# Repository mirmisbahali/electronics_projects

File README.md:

# LED Matrix PCB

A compact LED matrix prototyping board driven by an **Arduino Nano** using **charlieplexing** to control a large number of LEDs with minimal I/O pins.

## Status: 🚧 In Progress
- [x] Schematic complete
- [x] PCB layout complete
- [x] Fabrication files generated (JLCPCB) — parts ordered
- [ ] Testing

## Preview

### PCB View

> v1 design complete. Parts ordered from JLCPCB.

### Schematic

## Hardware
| Component | Details |
|-----------|---------|
| MCU | Arduino Nano |
| LED driver | Charlieplexing |
| Version | v1 |

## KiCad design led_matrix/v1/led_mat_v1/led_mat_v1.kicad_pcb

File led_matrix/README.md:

# LED Matrix PCB

A compact LED matrix prototyping board driven by an **Arduino Nano** using **charlieplexing** to control a large number of LEDs with minimal I/O pins.

## Status: 🚧 In Progress
- [x] Schematic complete
- [ ] PCB layout (component placement in progress)
- [ ] Fabrication
- [ ] Testing

## Preview

### PCB View

> Component placement and routing in progress.

### Schematic

## Hardware
| Component | Details |
|-----------|---------|
| MCU | Arduino Nano |
| LED driver | Charlieplexing |
| Version | v1 |

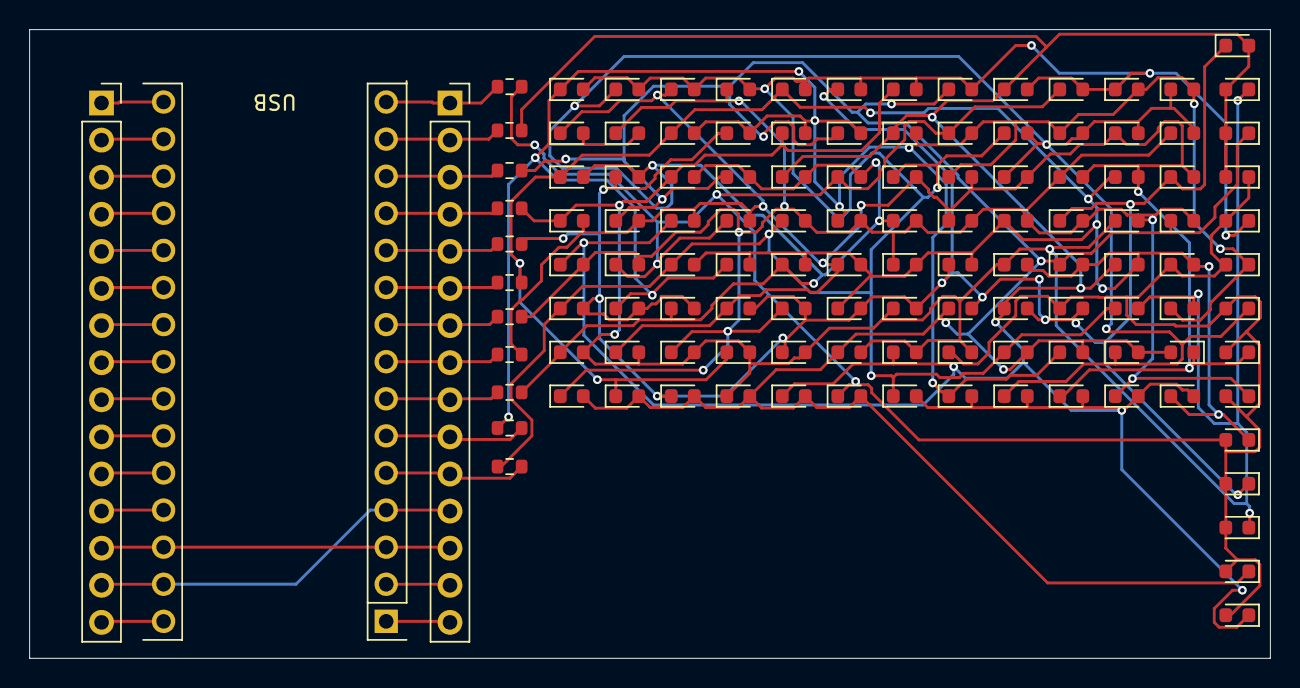
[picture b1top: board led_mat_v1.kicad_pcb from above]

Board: 2 copper layers, 85.0 x 43.1 mm, 124 parts (0 on the bottom side), 39 nets.

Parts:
A1: Arduino_Nano_Every; Arduino_Nano
D1, D2, D3, D4, D5, D6, D7, D8, D9, D10, D11, D12, D13, D14, D15, D16, D17, D18, D19, D20, D21, D22, D23, D24, D25, D26, D27, D28, D29, D30, D31, D32, D33, D34, D35, D36, D37, D38, D39, D40, D41, D42, D43, D44, D45, D46, D47, D48, D49, D50, D51, D52, D53, D54, D55, D56, D57, D58, D59, D60, D61, D62, D63, D64, D65, D66, D67, D68, D69, D70, D71, D72, D73, D74, D75, D76, D77, D78, D79, D80, D81, D82, D83, D84, D85, D86, D87, D88, D89, D90, D91, D92, D93, D94, D95, D96, D97, D98, D99, D100, D101, D102, D103, D104, D105, D106, D107, D108, D109, D110: LED; LED_0603_1608Metric
J1: Left_header; PinSocket_1x15_P2.54mm_Vertical
J2: Right_header; PinSocket_1x15_P2.54mm_Vertical
R1, R2, R3, R4, R5, R6, R7, R8, R9, R10, R11: 330; R_0603_1608Metric

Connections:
/3V3: A1.17 (3V3), J1.2
/5V OUT: A1.27 (+5V), J1.12
/A0/~D14: A1.19 (A0), J1.4
/A1/~D15: A1.20 (A1), J1.5
/A2/~D16: A1.21 (A2), J1.6
/A3/~D17: A1.22 (A3), J1.7
/A4/D~18: A1.23 (SDA/A4), J1.8
/A5/~D19: A1.24 (SCL/A5), J1.9
/A6/~D20: A1.25 (A6), J1.10
/A7/~D21: A1.26 (A7), J1.11
/AREF: A1.18 (AREF), J1.3
/D13: A1.16 (SCK), J1.1
/RESET: A1.3 (~RESET), A1.28 (~RESET), J1.13, J2.13
/VIN: A1.30 (VIN), J1.15
/~D0/TX: A1.1 (TX1), J2.15
/~D1/RX: A1.2 (RX1), J2.14
GND: A1.4 (GND), A1.29 (GND), J1.14, J2.12
unnamed: D1.2 (A), D2.2 (A), D3.2 (A), D4.2 (A), D5.2 (A), D6.2 (A), D7.2 (A), D8.2 (A), D9.2 (A), D10.2 (A), D11.1 (K), D21.1 (K), D31.1 (K), D41.1 (K), D51.1 (K), D61.1 (K), D71.1 (K), D81.1 (K), D91.1 (K), D101.1 (K), R1.2
unnamed: D1.1 (K), D11.2 (A), D12.2 (A), D13.2 (A), D14.2 (A), D15.2 (A), D16.2 (A), D17.2 (A), D18.2 (A), D19.2 (A), D20.2 (A), D22.1 (K), D32.1 (K), D42.1 (K), D52.1 (K), D62.1 (K), D72.1 (K), D82.1 (K), D92.1 (K), D102.1 (K), R2.2
unnamed: D10.1 (K), D20.1 (K), D30.1 (K), D40.1 (K), D50.1 (K), D60.1 (K), D70.1 (K), D80.1 (K), D90.1 (K), D100.1 (K), D101.2 (A), D102.2 (A), D103.2 (A), D104.2 (A), D105.2 (A), D106.2 (A), D107.2 (A), D108.2 (A), D109.2 (A), D110.2 (A), R11.2
unnamed: D9.1 (K), D19.1 (K), D29.1 (K), D39.1 (K), D49.1 (K), D59.1 (K), D69.1 (K), D79.1 (K), D89.1 (K), D91.2 (A), D92.2 (A), D93.2 (A), D94.2 (A), D95.2 (A), D96.2 (A), D97.2 (A), D98.2 (A), D99.2 (A), D100.2 (A), D110.1 (K), R10.2
unnamed: D2.1 (K), D12.1 (K), D21.2 (A), D22.2 (A), D23.2 (A), D24.2 (A), D25.2 (A), D26.2 (A), D27.2 (A), D28.2 (A), D29.2 (A), D30.2 (A), D33.1 (K), D43.1 (K), D53.1 (K), D63.1 (K), D73.1 (K), D83.1 (K), D93.1 (K), D103.1 (K), R3.2
unnamed: D3.1 (K), D13.1 (K), D23.1 (K), D31.2 (A), D32.2 (A), D33.2 (A), D34.2 (A), D35.2 (A), D36.2 (A), D37.2 (A), D38.2 (A), D39.2 (A), D40.2 (A), D44.1 (K), D54.1 (K), D64.1 (K), D74.1 (K), D84.1 (K), D94.1 (K), D104.1 (K), R4.2
unnamed: D4.1 (K), D14.1 (K), D24.1 (K), D34.1 (K), D41.2 (A), D42.2 (A), D43.2 (A), D44.2 (A), D45.2 (A), D46.2 (A), D47.2 (A), D48.2 (A), D49.2 (A), D50.2 (A), D55.1 (K), D65.1 (K), D75.1 (K), D85.1 (K), D95.1 (K), D105.1 (K), R5.2
unnamed: D5.1 (K), D15.1 (K), D25.1 (K), D35.1 (K), D45.1 (K), D51.2 (A), D52.2 (A), D53.2 (A), D54.2 (A), D55.2 (A), D56.2 (A), D57.2 (A), D58.2 (A), D59.2 (A), D60.2 (A), D66.1 (K), D76.1 (K), D86.1 (K), D96.1 (K), D106.1 (K), R6.2
unnamed: D6.1 (K), D16.1 (K), D26.1 (K), D36.1 (K), D46.1 (K), D56.1 (K), D61.2 (A), D62.2 (A), D63.2 (A), D64.2 (A), D65.2 (A), D66.2 (A), D67.2 (A), D68.2 (A), D69.2 (A), D70.2 (A), D77.1 (K), D87.1 (K), D97.1 (K), D107.1 (K), R7.2
unnamed: D7.1 (K), D17.1 (K), D27.1 (K), D37.1 (K), D47.1 (K), D57.1 (K), D67.1 (K), D71.2 (A), D72.2 (A), D73.2 (A), D74.2 (A), D75.2 (A), D76.2 (A), D77.2 (A), D78.2 (A), D79.2 (A), D80.2 (A), D88.1 (K), D98.1 (K), D108.1 (K), R8.2
unnamed: D8.1 (K), D18.1 (K), D28.1 (K), D38.1 (K), D48.1 (K), D58.1 (K), D68.1 (K), D78.1 (K), D81.2 (A), D82.2 (A), D83.2 (A), D84.2 (A), D85.2 (A), D86.2 (A), D87.2 (A), D88.2 (A), D89.2 (A), D90.2 (A), D99.1 (K), D109.1 (K), R9.2
Row 1: A1.5 (D2), J2.11, R1.1
Row 2: A1.6 (D3), J2.10, R2.1
Row 3: A1.7 (D4), J2.9, R3.1
Row 4: A1.8 (D5), J2.8, R4.1
Row 5: A1.9 (D6), J2.7, R5.1
Row 6: A1.10 (D7), J2.6, R6.1
Row 7: A1.11 (D8), J2.5, R7.1
Row 8: A1.12 (D9), J2.4, R8.1
Row 9: A1.13 (D10), J2.3, R9.1
Row 10: A1.14 (MOSI), J2.2, R10.1
Row 11: A1.15 (MISO), J2.1, R11.1

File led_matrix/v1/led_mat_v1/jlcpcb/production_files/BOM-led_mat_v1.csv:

Comment,Designator,Footprint,LCSC,Quantity
330,"R1,R10,R11,R2,R3,R4,R5,R6,R7,R8,R9",R_0603_1608Metric,C23138,11
LED,"D1,D10,D100,D101,D102,D103,D104,D105,D106,D107,D108,D109,D11,D110,D12,D13,D14,D15,D16,D17,D18,D19,D2,D20,D21,D22,D23,D24,D25,D26,D27,D28,D29,D3,D30,D31,D32,D33,D34,D35,D36,D37,D38,D39,D4,D40,D41,D42,D43,D44,D45,D46,D47,D48,D49,D5,D50,D51,D52,D53,D54,D55,D56,D57,D58,D59,D6,D60,D61,D62,D63,D64,D65,D66,D67,D68,D69,D7,D70,D71,D72,D73,D74,D75,D76,D77,D78,D79,D8,D80,D81,D82,D83,D84,D85,D86,D87,D88,D89,D9,D90,D91,D92,D93,D94,D95,D96,D97,D98,D99",LED_0603_1608Metric,C2286,110
Right_header,J2,PinSocket_1x15_P2.54mm_Vertical,,1
Arduino_Nano_Every,A1,Arduino_Nano,,1
Left_header,J1,PinSocket_1x15_P2.54mm_Vertical,,1

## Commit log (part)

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2026-05-04 added test1 inside pcb_tutorials
2026-05-04 feat(led_matrix): add LED matrix PCB project v1 - schematic and initial PCB layout
    - Created KiCad project 'led_mat_v1' for a LED matrix board (version 1)
    - Drew complete schematic including LED array, current-limiting resistors,
    and control signal routing
    - Placed LEDs on PCB editor canvas in matrix arrangement; board outline and
    component placement in progress
    - Added calculations.xlsx with LED current, resistor value, and power budget
2026-05-04 docs(led_matrix): add README with project overview and image placeholders
2026-05-04 docs(led_matrix): add placement and routing status note under PCB view
2026-05-04 feat(led_matrix): add PCB/schematic exports and update KiCad project files
    - Add 3D PCB view export (led_mat_v1.png) and schematic export (led_mat_v1.svg)
    - Update schematic, PCB layout, and project files with latest design changes
    - Exclude KiCad lock files (*.lck) from version control via .gitignore
2026-05-04 moved readme to repository level
2026-05-04 Fix image paths in README.md
    Updated image paths for PCB View and Schematic in README.
2026-05-05 feat(led_matrix): complete v1 design and add JLCPCB production files
    PCB layout and routing finalized. Added gerbers, BOM, and CPL files for
    JLCPCB fabrication. Parts ordered. Includes placement helper scripts.
    Updated README status to reflect design completion and order placed.
2026-05-16 feat(pcb_business_card): add v1 schematic, firmware config, datasheets, and component libraries
    Includes KiCad schematic with STM32L031G6U6 MCU, LIS2DW12 accelerometer,
    ST25DV04K NFC chip, 8x8 charlieplexed LED matrix, and CR2032 battery circuit.
    Also adds STM32CubeMX IOC config, 6 reference datasheets, and custom LIS2DW12
    KiCad symbol and LGA-12 footprint variants.
